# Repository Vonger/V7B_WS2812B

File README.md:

### Compile Firmware
1. download wch riscv toolchain from its offical site(http://www.mounriver.com/download, select Linux).
2. call **make** to compile the firmware.
3. call **make flash** to upload firmware to device.(hardware requires WCH-LinkE, PD1 to SWDIO)
4. call **make test** to create the local test application.
5. run test, check result on dashboard.

note: IS31FL3731 compatible mode register address only use 1bytes, so max supported LEDs are 72 RGB LEDs(or 216 single color LEDs). Not compatible mode has two bytes for address, so max supported LEDs are 512 RGB LEDs or more(depends on the memory to buffer the LED data)

- ws2812b.is31.bin: this is compatible IS31FL3731 firmware.
- ws2812b.full.bin: this is not compatible but can use all ws2812b in line firmware.

### Link

 - Compile in Ubuntu 22.04
 - WCH CH32V003 RISCV toolchain: http://www.mounriver.com/download => Linux => MRS_Toolchain_Linux_x64_VX.XX.tar.xz
 - install libjlink0 for openocd(sudo apt install libjlink0).

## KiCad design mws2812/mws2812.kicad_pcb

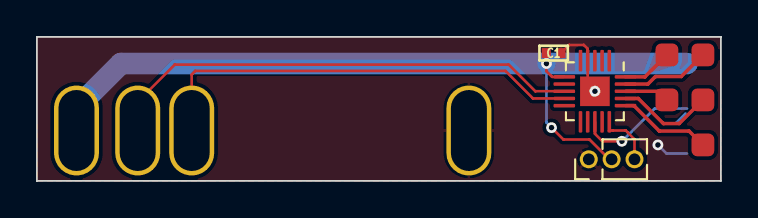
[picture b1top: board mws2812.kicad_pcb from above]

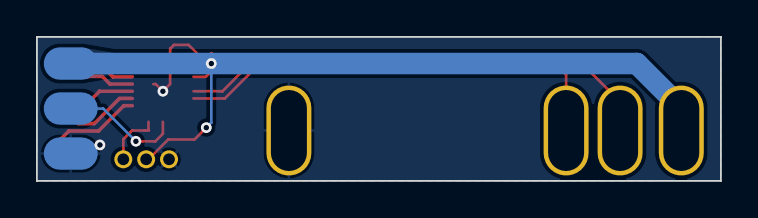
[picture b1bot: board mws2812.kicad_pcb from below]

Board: 2 copper layers, 38.0 x 8.0 mm, 15 parts (7 on the bottom side), 11 nets.

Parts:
C1: 100nF; 0402C
J1: Conn_01x01; TestPoint_Hole_4.0x2.0mm
J2: Conn_01x03_Socket; PinHeader_1x03_P1.27mm_Vertical
J3, J4, J5: Conn_01x01; TestPoint_Pad_3.0x2.0mm
J6, J7, J8: Conn_01x01; TestPoint_Hole_5.0x2.5mm
J9, J10, J11, J12, J13: Conn_01x01_Socket; TestPoint_Pad_D1.0mm
U3: CH32V003F4U6; QFN-20-1EP_3x3mm_P0.4mm_EP1.65x1.65mm

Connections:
+5V: C1.1, J1.1, J2.2, J5.1, U3.6 (VDD)
DEBUG: J2.3, U3.15 (PD1)
DOUT: J4.1, U3.13 (PC6)
GND: C1.2, J2.1, J3.1, J8.1, U3.4 (VSS), U3.21 (GND)
PD2: J9.1, U3.16 (PD2)
PD3: J10.1, U3.17 (PD3)
PD4: J11.1, U3.18 (PD4)
PD5: J12.1, U3.19 (PD5)
PD6: J13.1, U3.20 (PD6)
SCK: J7.1, U3.9 (PC2)
SDA: J6.1, U3.8 (PC1)

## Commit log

2023-11-04 first version for i2c ws2812.
2023-11-05 fix second led flash sometimes because of the reset too short.
2023-11-05 update max support LED to 512.
2023-11-05 fix byte order.
2023-11-23 spi use one pin only PC6.
2023-11-25 update unit test to avoid flash.
2023-11-25 update comment.
2023-11-27 put globle data to bss to clear.
2023-11-27 set spi interrupt higher than i2c.
2023-11-27 reduce led number.
2023-11-28 simplify code.
2023-11-29 fix interrupt priority casued led flash.
2023-11-29 final solution of interrupt flash issue.
2023-12-05 add IS31FL3731 compatible.
2023-12-07 simplify Makefile.
2023-12-08 update reset time to compatible more ws2812b.
2023-12-08 add ch32v003 library to source.
2023-12-08 disable unit test.
2023-12-09 fix i2c reg byte order.
2023-12-09 fix IS31FL3731 compatible mode.
2023-12-09 add led test code.
2023-12-09 update LED flash speed.
2023-12-09 add README.md
2023-12-12 fix comment.
2024-01-13 change test output file name to ledtest.
2024-04-18 fix warning and increase led speed.
2024-06-18 add compiled bin file.
2024-06-24 add full mode firmware, not compatible is31fl3731.
2025-08-12 update path in Makefile.
2025-09-22 update test mode with more details.
2025-09-24 slow the flash speed.
2025-10-13 update test to support new LED mode.
2025-10-13 add usleep for enough reset time.
2025-11-11 update test mode.
2025-11-19 add driver board sch and pcb.
